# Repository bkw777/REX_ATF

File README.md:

# NOT WORKING

If you just want a REX, buy a [REX#](https://bitchin100.com/wiki/index.php?title=REXsharp) or build a [REX Classic](https://github.com/bkw777/REX_Classic).

This is is an attempt to port REX Classic to a different CPLD chip.  
REX Classic is built around the Xilinx XCR3064XL, which is discontinued.  
ATF1504ASL is a similar part that is still available.  
Do not bother trying to build this yet unless you actually want to help GET it working.  
Because it DOES NOT WORK yet. But it seems to be close...  

## Current Status

Can't figure out a way to replicate the Xilinx internal pullup feature while using the Quartus -> EPM7064S -> POF2JED workflow, so at least for now we have external pullup resistors on the CSA & CSB pins (formerly TP1 & TP2). All other pins should be ok since they are connected to the bus.

Quartus 13.0 compiles the VHDL and creates `rexbrd.pof`.  
`pof2jed` creates `rexbrd.jed`.  
`atmisp` creates `rexbrd.svf`.  
`openocd` programs `rexbrd.svf` to the device.  

The machine still runs normally with the REX installed, so at least the REX is not waking up and interfering with the bus when not selected.

`rf149.co` runs without error.  
The "wiping blocks" stage goes way too fast.  
`CALL 63012` hangs.

TODO: observe the bus with https://github.com/bkw777/Molex_7880x_bus_tap

----
# REX_ATF

[REX Classic](http://tandy.wiki/REX) built on Microchip ATF1504 instead of Xilinx XCR3064

# What is it?

REX Classic is an on-board software-controlled rom library for TRS-80 Model 100, 102, or 200.

REX was originally designed around a Xilinx XCR3064XL CPLD, but Xilinx has stopped producing those.

This is a version of REX Classic using the same VHDL code, but compiled for a Microchip ATF1504ASL CPLD, which is still an active part.

# BOM

1 x ATF1504ASL TQFP44 - CPLD 64MC 5V  
https://www.digikey.com/en/products/detail/microchip-technology/ATF1504ASL-25AU44/1008353

1 x 29F800BB TSOP48 ex: AM29F800BB, M29F800FB, MX29F800CB - 8Mx8/4Mx16 FLASH parallel 5V bottom-boot  
https://www.digikey.com/en/products/detail/alliance-memory-inc/M29F800FB5AN6F2/12180108

2 x 1uF MLCC 0805 16V+  
https://www.digikey.com/en/products/detail/yageo/CC0805KKX7R7BB105/2103103

Gerbers & CPLD bitstream in [releases](../../releases/latest). (not working yet, so no release yet)

Carrier: https://shop.jawstec.com/3d-printed-molex-78802-pcb-carrier_p641.php?id=641  
(https://github.com/bkw777/Molex78802_Module/blob/master/Carrier/Molex78802_PCB_28.stl)

# Programming the CPLD
Install [openocd](https://openocd.org/) and a wrapper script [atfsvf](https://github.com/bkw777/ATF150x_uDEV/blob/main/bin/atfsvf):  
```
$ sudo apt install openocd
$ wget https://github.com/bkw777/ATF150x_uDEV/raw/main/bin/atfsvf
$ install -m 755 atfsvf ~/.local/bin/
```

Programmer hardware:  
 * [FT232R or FT232H usb-ttl module that can supply 5V VCC](https://github.com/bkw777/ATF150x_uDEV/blob/main/programming.md#hardware)
 * 6-pin length of generic 2.54mm single row square male pin header
 * 6 female dupont wires
 * [connection pinout table](https://github.com/bkw777/ATF150x_uDEV/blob/main/programming.md#hardware)

Example using an [FT232R usbc-ttl-serial module](https://amazon.com/dp/B0CQVB6JFV)  

Get the SVF file from [Releases](../../releases/latest). (No releases yet since it doesn't work yet)

Use the atfsvf script to program the chip with the svf.  
If you have a FT232H module instead of FT232R, then change ft232r to ft232h below.  
`$ atfsvf ft232r ATF1504ASL rexbrd.svf`

# Usage
Use the normal [REX Classic](http://bitchin100.com/wiki/index.php?title=REXclassic) software and documentation.

Example on linux:

## install [dl2](https://github.com/bkw777/dl2)
```
$ git clone https://github.com/bkw777/dl2.git
$ cd dl2 && make clean all && sudo make install
```

## connect 100 to pc by serial
reference: http://tandy.wiki/Model_T_Serial_Cable  
https://www.pccables.com/products/00103.html  
https://www.amazon.com/gp/product/B074VN9ZG4/  

## load the REX firmware
```
$ wget https://www.bitchin100.com/wiki/images/3/38/R49_M100T102_260_rebuild.zip
$ unzip R49_M100T102_260_rebuild.zip
$ co2ba rf149.co call >rf149.do
$ dl -vb rf149.do && dl -vu
```
(follow the on-screen directions in the terminal and on the 100)  
Then SHIFT+BREAK+RESET on the 100  
Then Power-cycle the 100  

## Try to activate the REX
In BASIC: `CALL 63012`  
(currently hangs)

# Generating the SVF from the VHDL source

# Credits
Original REX design is by Steven Adolph  
http://bitchin100.com/wiki/index.php?title=REX  
http://www.club100.org/memfiles/index.php?direction=0&order=&directory=Steve%20Adolph

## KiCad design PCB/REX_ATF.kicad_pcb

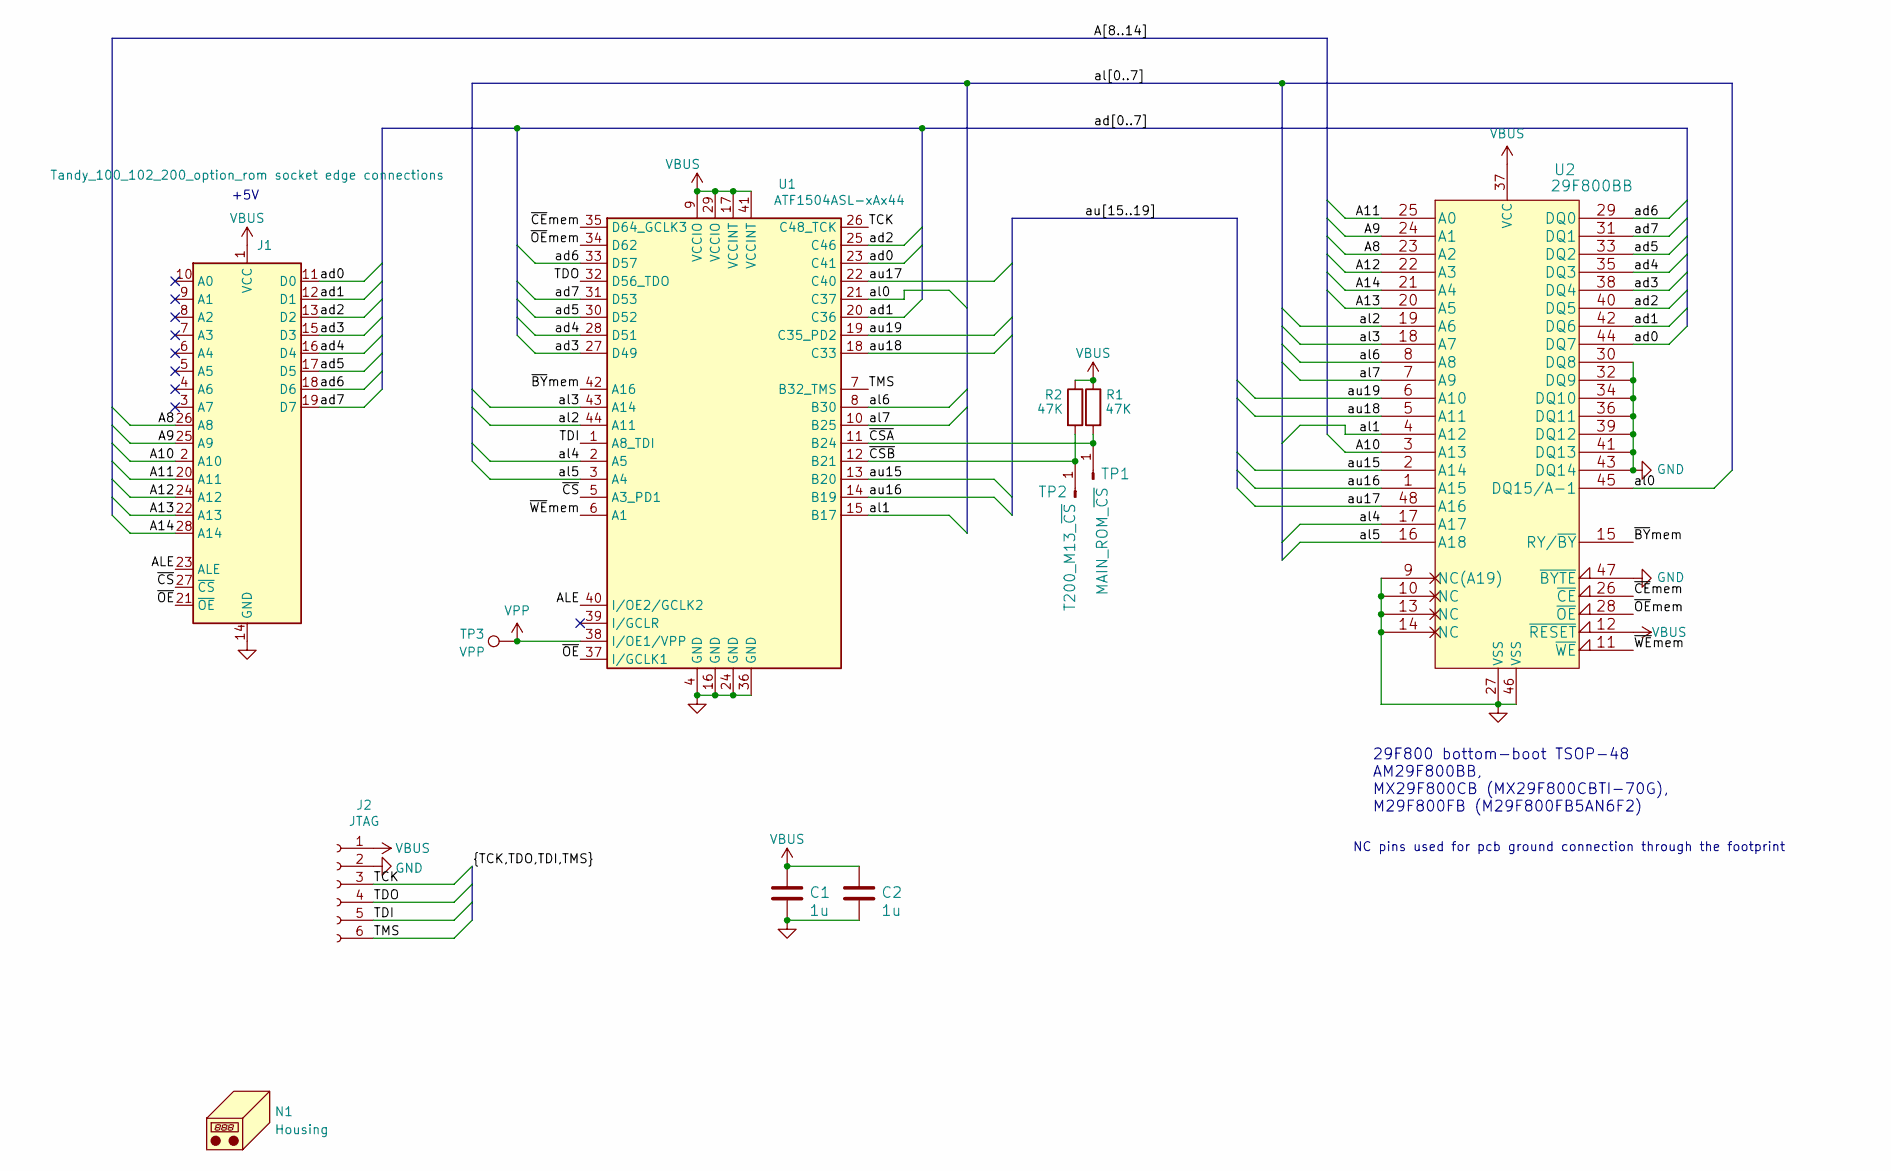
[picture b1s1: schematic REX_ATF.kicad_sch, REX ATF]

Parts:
C1, C2: 1u; C_0805; MPN CL21B105KAFNNNE
J1: Tandy_100_102_200_option_rom socket edge connecti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; Molex78802_PCB_28_REX
J2: JTAG; 1x6_pcb_socket
N1: Housing; Housing_Molex78802_PCB_28
R1, R2: 47K; R_0805; MPN RC0805JR-0747KL
TP1: MAIN_ROM_~{CS}; 1x1_pin_h
TP2: T200_M13_~{CS}; 1x1_pin_h
TP3: VPP; TP_D0.8
U1: ATF1504ASL-xAx44; VQFP44; MPN ATF1504ASL-25AU44
U2: 29F800BB; TSOP-48; MPN M29F800FB5AN6F2

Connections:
/A8: J1.26 (A8), U2.23 (A2)
/A9: J1.25 (A9), U2.24 (A1)
/A10: J1.2 (A10), U2.3 (A13)
/A11: J1.20 (A11), U2.25 (A0)
/A12: J1.24 (A12), U2.22 (A3)
/A13: J1.22 (A13), U2.20 (A5)
/A14: J1.28 (A14), U2.21 (A4)
/ALE: J1.23 (ALE), U1.40 (I/OE2/GCLK2)
/TCK: J2.3, U1.26 (C48_TCK)
/TDI: J2.5, U1.1 (A8_TDI)
/TDO: J2.4, U1.32 (D56_TDO)
/TMS: J2.6, U1.7 (B32_TMS)
/ad0: J1.11 (D0), U1.23 (C41), U2.44 (DQ7)
/ad1: J1.12 (D1), U1.20 (C36), U2.42 (DQ6)
/ad2: J1.13 (D2), U1.25 (C46), U2.40 (DQ5)
/ad3: J1.15 (D3), U1.27 (D49), U2.38 (DQ4)
/ad4: J1.16 (D4), U1.28 (D51), U2.35 (DQ3)
/ad5: J1.17 (D5), U1.30 (D52), U2.33 (DQ2)
/ad6: J1.18 (D6), U1.33 (D57), U2.29 (DQ0)
/ad7: J1.19 (D7), U1.31 (D53), U2.31 (DQ1)
/al0: U1.21 (C37), U2.45 (DQ15/A-1)
/al1: U1.15 (B17), U2.4 (A12)
/al2: U1.44 (A11), U2.19 (A6)
/al3: U1.43 (A14), U2.18 (A7)
/al4: U1.2 (A5), U2.17 (A17)
/al5: U1.3 (A4), U2.16 (A18)
/al6: U1.8 (B30), U2.8 (A8)
/al7: U1.10 (B25), U2.7 (A9)
/au15: U1.13 (B20), U2.2 (A14)
/au16: U1.14 (B19), U2.1 (A15)
/au17: U1.22 (C40), U2.48 (A16)
/au18: U1.18 (C33), U2.5 (A11)
/au19: U1.19 (C35_PD2), U2.6 (A10)
/~BYmem: U1.42 (A16), U2.15 (RY/~BY)
/~CEmem: U1.35 (D64_GCLK3), U2.26 (~CE)
/~CSA: R1.2, TP1.1, U1.11 (B24)
/~CSB: R2.2, TP2.1, U1.12 (B21)
/~CS: J1.27 (~CS), U1.5 (A3_PD1)
/~OE: J1.21 (~OE), U1.37 (I/GCLK1)
/~OEmem: U1.34 (D62), U2.28 (~OE)
/~WEmem: U1.6 (A1), U2.11 (~WE)
GND: C1.2, C2.2, J1.14 (GND), J2.2, U1.4 (GND), U1.16 (GND), U1.24 (GND), U1.36 (GND), U2.9 (NC(A19)), U2.10 (NC), U2.13 (NC), U2.14 (NC), U2.27 (VSS), U2.30 (DQ8), U2.32 (DQ9), U2.34 (DQ10), U2.36 (DQ11), U2.39 (DQ12), U2.41 (DQ13), U2.43 (DQ14), U2.46 (VSS), U2.47 (~BYTE)
VBUS: C1.1, C2.1, J1.1 (VCC), J2.1, R1.1, R2.1, U1.9 (VCCIO), U1.17 (VCCINT), U1.29 (VCCIO), U1.41 (VCCINT), U2.12 (~RESET), U2.37 (VCC)
VPP: TP3.1, U1.38 (I/OE1/VPP)

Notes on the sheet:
+5V
29F800 bottom-boot TSOP-48 AM29F800BB, MX29F800CB (MX29F800CBTI-70G), M29F800FB (M29F800FB5AN6F2)
NC pins used for pcb ground connection through the footprint

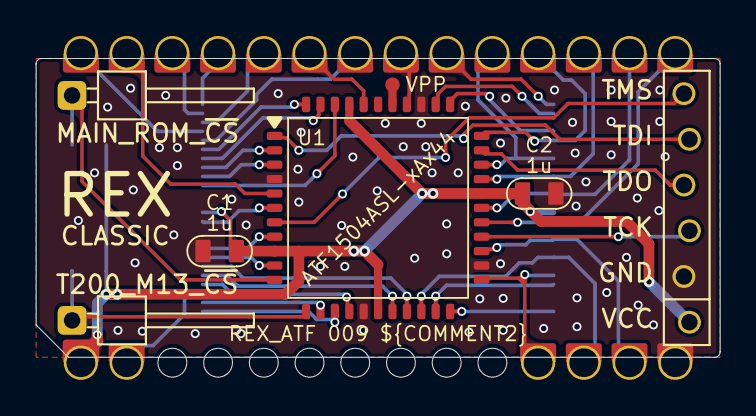
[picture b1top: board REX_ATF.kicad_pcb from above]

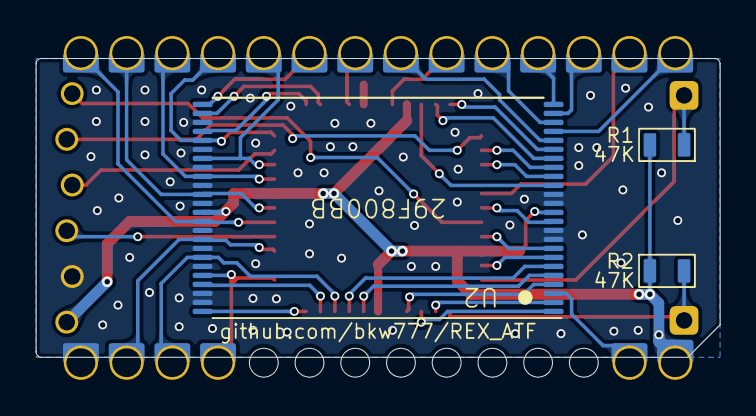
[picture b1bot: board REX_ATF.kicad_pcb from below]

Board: 2 copper layers, 38.0 x 16.6 mm, 12 parts (3 on the bottom side), 44 nets.

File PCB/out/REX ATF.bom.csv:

"Reference","Value","Datasheet","Footprint","Qty","DNP","MPN","Description"
"C1,C2","1u","datasheets/CL21B105KAFNNNE.pdf","000_LOCAL:C_0805","2","","CL21B105KAFNNNE","1 µF ±10% 25V Ceramic Capacitor X7R 0805"
"R1,R2","47K","datasheets/PYU-RC_GROUP_51_ROHS_L.pdf","000_LOCAL:R_0805","2","","RC0805JR-0747KL","R 47k 0805"
"U1","ATF1504ASL-xAx44","datasheets/ATF1504AS.pdf","000_LOCAL:VQFP44","1","","ATF1504ASL-25AU44","ATMEL Altera Microchip 64-Macrocell CPLD, VQFP-44"
"U2","29F800BB","datasheets/M29F800.pdf","000_LOCAL:TSOP-48","1","","M29F800FB5AN6F2","FLASH - NOR Memory IC 1Mx8 512Kx16 Parallel 5v 48-TSOP"

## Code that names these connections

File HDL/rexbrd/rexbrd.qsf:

# -------------------------------------------------------------------------- #
#
# Copyright (C) 1991-2013 Altera Corporation
# Your use of Altera Corporation's design tools, logic functions 
# and other software and tools, and its AMPP partner logic 
# functions, and any output files from any of the foregoing 
# (including device programming or simulation files), and any 
# associated documentation or information are expressly subject 
# to the terms and conditions of the Altera Program License 
# Subscription Agreement, Altera MegaCore Function License 
# Agreement, or other applicable license agreement, including, 
# without limitation, that your use is for the sole purpose of 
# programming logic devices manufactured by Altera and sold by 
# Altera or its authorized distributors.  Please refer to the 
# applicable agreement for further details.
#
# -------------------------------------------------------------------------- #
#
# Quartus II 64-Bit
# Version 13.0.1 Build 232 06/12/2013 Service Pack 1 SJ Web Edition
# Date created = 17:39:42  July 08, 2024
#
# -------------------------------------------------------------------------- #
#
# Notes:
#
# 1) The default values for assignments are stored in the file:
#		rexbrd_assignment_defaults.qdf
#    If this file doesn't exist, see file:
#		assignment_defaults.qdf
#
# 2) Altera recommends that you do not modify this file. This
#    file is updated automatically by the Quartus II software
#    and any changes you make may be lost or overwritten.
#
# -------------------------------------------------------------------------- #


set_global_assignment -name FAMILY MAX7000S
set_global_assignment -name DEVICE "EPM7064STC44-10"
set_global_assignment -name TOP_LEVEL_ENTITY rexbrd
set_global_assignment -name ORIGINAL_QUARTUS_VERSION "13.0 SP1"
set_global_assignment -name PROJECT_CREATION_TIME_DATE "17:39:42  JULY 08, 2024"
set_global_assignment -name LAST_QUARTUS_VERSION "13.0 SP1"
set_global_assignment -name PROJECT_OUTPUT_DIRECTORY output_files
set_global_assignment -name DEVICE_FILTER_PACKAGE TQFP
set_global_assignment -name DEVICE_FILTER_PIN_COUNT 44
set_global_assignment -name ERROR_CHECK_FREQUENCY_DIVISOR "-1"
set_global_assignment -name EDA_SIMULATION_TOOL "ModelSim-Altera (VHDL)"
set_global_assignment -name EDA_OUTPUT_DATA_FORMAT VHDL -section_id eda_simulation
set_location_assignment PIN_30 -to ad[5]
set_location_assignment PIN_19 -to au[19]
set_location_assignment PIN_23 -to ad[0]
set_location_assignment PIN_2 -to al[4]
set_location_assignment PIN_13 -to au[15]
set_location_assignment PIN_28 -to ad[4]
set_location_assignment PIN_21 -to al[0]
set_location_assignment PIN_10 -to al[7]
set_location_assignment PIN_33 -to ad[6]
set_location_assignment PIN_18 -to au[18]
set_location_assignment PIN_3 -to al[5]
set_location_assignment PIN_14 -to au[16]
set_location_assignment PIN_20 -to ad[1]
set_location_assignment PIN_43 -to al[3]
set_location_assignment PIN_27 -to ad[3]
set_location_assignment PIN_15 -to al[1]
set_location_assignment PIN_8 -to al[6]
set_location_assignment PIN_31 -to ad[7]
set_location_assignment PIN_22 -to au[17]
set_location_assignment PIN_25 -to ad[2]
set_location_assignment PIN_44 -to al[2]
set_global_assignment -name MAX7000_DEVICE_IO_STANDARD TTL
set_global_assignment -name OPTIMIZE_HOLD_TIMING OFF
set_global_assignment -name OPTIMIZE_MULTI_CORNER_TIMING OFF
set_global_assignment -name FITTER_EFFORT "STANDARD FIT"
set_global_assignment -name USE_CONFIGURATION_DEVICE ON
set_global_assignment -name MAX7000_USE_CHECKSUM_AS_USERCODE ON
set_global_assignment -name VHDL_SHOW_LMF_MAPPING_MESSAGES OFF
set_global_assignment -name ENABLE_DRC_SETTINGS ON
set_location_assignment PIN_6 -to WEmem
set_location_assignment PIN_42 -to BYmem
set_location_assignment PIN_40 -to ALE
set_location_assignment PIN_34 -to OEmem
set_location_assignment PIN_12 -to CSB
set_location_assignment PIN_37 -to OE
set_location_assignment PIN_35 -to CEmem
set_location_assignment PIN_11 -to CSA

set_global_assignment -name VHDL_FILE regis.vhd
set_global_assignment -name VHDL_FILE regis_vector.vhd
set_global_assignment -name VHDL_FILE rexbrd.vhd

set_location_assignment PIN_5 -to CS
set_global_assignment -name RESERVE_ALL_UNUSED_PINS_NO_OUTPUT_GND "AS INPUT TRI-STATED"

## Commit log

2024-07-21 initial
2024-07-22 move some traces around
2024-07-22 remove junk file
2024-07-22 readme
2024-07-22 docs
2024-07-23 use nc pins for pcb ground path
2024-07-24 move ALE to a GCLK pin and init /CSA & /CSB high
2024-07-24 include build results until we start doing releases
2024-07-25 external pullups on CSA CSB
2024-08-01 enable pin keeper option
2025-02-10 gitignore
2026-04-12 minor pcb touches, update readme
2026-04-12 update pinout in vhdl to match pcb
